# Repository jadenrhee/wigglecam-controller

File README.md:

# WiggleCam Camera Controller

The RP2040 board that handles timing-critical and analog work for a
[4-lens camera](https://github.com/jadenrhee/wigglecam). The Raspberry
Pi runs capture and image processing, but Linux is not a real-time OS
and the Pi can't drive the flash directly.

This board runs the LED flash at constant current, with the limits set
in the circuit rather than only in firmware. It also debounces the
shutter, decodes the EC11 encoder, and monitors battery voltage and
current through an INA219. On a trigger it pulses the Pi the instant the
LEDs reach full current.

The Pi drives it over I2C at 0x17, and the capture pulse returns on its
own GPIO line. The 2x6 header maps 1:1 onto Pi 5 GPIO pins 1 to 12.

Not fabricated yet, so everything here comes from the design files.

Signal routing, front copper red and back copper blue, planes hidden:

| | |
|---|---|
| Board | 76 x 50 mm, 4 layers |
| Schematic | ERC clean, 0 errors and 0 warnings |
| Layout | DRC clean, 0 violations and 0 unconnected, against JLCPCB's published 4-layer rules |
| Verification | 24 checks measured off the finished layout, no failures. [Report](docs/verification-report.md) |
| Firmware | builds clean under the Pico SDK |
| Fab outputs | Gerbers, drill, BOM, and placement files in [fab/](fab/); the ready-to-upload set is [fab/jlc/](fab/jlc/) |

## Repo layout

| Path | Contents |
|------|----------|
| [hardware/skidl/](hardware/skidl/) | schematic as code, the source of record |
| [hardware/kicad/](hardware/kicad/) | the board file and custom footprints |
| [hardware/partlist.md](hardware/partlist.md) | every part, the reasoning behind it, and where to order it |
| [fab/](fab/) | Gerbers, Excellon drill, `bom.csv`, `cpl.csv`, renders |
| [firmware/](firmware/) | C firmware: I2C register file, flash safety logic, INA219, EC11, WS2812 |
| [enclosure/](enclosure/) | 3D-printable pod holding the screen, this board, and the Pi 5 |
| [docs/](docs/) | [verification report](docs/verification-report.md), [design rationale](docs/design-rationale.md), and the [Pi protocol](docs/protocol.md) |

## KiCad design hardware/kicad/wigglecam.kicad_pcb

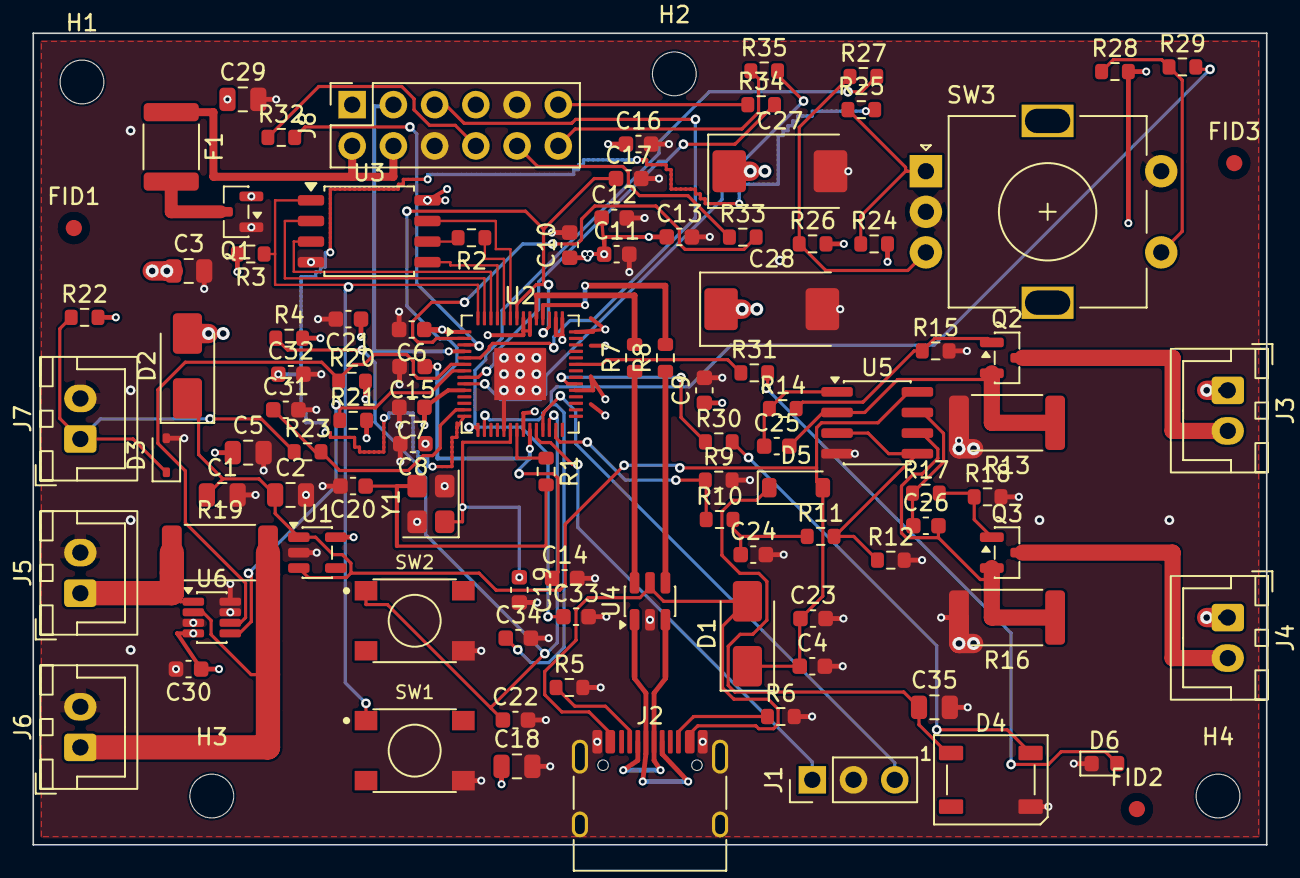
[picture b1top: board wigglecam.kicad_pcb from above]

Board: 4 copper layers, 76.0 x 50.0 mm, 105 parts (0 on the bottom side), 67 nets.

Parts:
C1, C2: 22uF; C_0805_2012Metric
C3, C5, C18, C29, C35: 10uF; C_0805_2012Metric
C4, C16, C17, C24: 1uF; C_0603_1608Metric
C6, C7, C8, C9, C10, C11, C12, C13, C14, C15, C21, C22, C23, C30, C31, C32, C33, C34: 100nF; C_0603_1608Metric
C19, C20: 15pF; C_0603_1608Metric
C25, C26: 1nF; C_0603_1608Metric
C27, C28: 470uF; CP_EIA-7343-30_AVX-N
D1, D2: SS34; D_SMA
D3: PESD5V0S1BA; D_SOD-323
D4: WS2812B; LED_WS2812B_PLCC4_5.0x5.0mm_P3.2mm
D5: 1N4148W; D_SOD-123
D6: GREEN; LED_0603_1608Metric
F1: PTC 3A; Fuse_1812_4532Metric
FID1, FID2, FID3: Fiducial_1mm_Mask2mm
H1, H2, H3, H4: MountingHole_2.7mm_M2.5
J1: SWD; PinHeader_1x03_P2.54mm_Vertical
J2: USB-C; USB_C_Receptacle_HRO_TYPE-C-31-M-12
J3: LED1; JST_XH_B2B-XH-A_1x02_P2.50mm_Vertical
J4: LED2; JST_XH_B2B-XH-A_1x02_P2.50mm_Vertical
J5: VBAT_IN; JST_XH_B2B-XH-A_1x02_P2.50mm_Vertical
J6: VBAT_OUT; JST_XH_B2B-XH-A_1x02_P2.50mm_Vertical
J7: SHUTTER; JST_XH_B2B-XH-A_1x02_P2.50mm_Vertical
J8: Pi GPIO 1-12; PinSocket_2x06_P2.54mm_Vertical
Q1: AO3401A; SOT-23
Q2, Q3: AO3400A; SOT-23
R1, R10, R23, R25, R27, R29, R31: 1k; R_0603_1608Metric
R2, R7, R8: 27R; R_0603_1608Metric
R3, R4, R22, R24, R26, R28: 10k; R_0603_1608Metric
R5, R6: 5.1k; R_0603_1608Metric
R9, R15, R18: 100k; R_0603_1608Metric
R11: 5.6k; R_0603_1608Metric
R12: 1.2k; R_0603_1608Metric
R13, R16: 0.5R 1%; R_2512_6332Metric
R14, R17: 100R; R_0603_1608Metric
R19: 10mR 2W 1%; R_2512_6332Metric
R20, R21: 4.7k; R_0603_1608Metric
R30: 470R; R_0603_1608Metric
R32, R33, R34, R35: 330R; R_0603_1608Metric
SW1, SW2: TACT; SW_TS-1187A_5.1x5.1mm
SW3: EC11; RotaryEncoder_Alps_EC11E-Switch_Vertical_H20mm
U1: AP2112K-3.3; SOT-23-5
U2: RP2040; QFN-56-1EP_7x7mm_P0.4mm_EP3.2x3.2mm
U3: W25Q128JVSIQ; SOIC-8_5.3x5.3mm_P1.27mm
U4: USBLC6-2SC6; SOT-23-6
U5: LM358; SOIC-8_3.9x4.9mm_P1.27mm
U6: INA219; SOT-23-8
Y1: 12MHz; Crystal_SMD_3225-4Pin_3.2x2.5mm

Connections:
+3V3: C5.1, C6.1, C7.1, C8.1, C9.1, C10.1, C11.1, C12.1, C13.1, C16.1, C18.1, C21.1, C30.1, R3.2, R4.2, R20.2, R21.2, R22.2, R24.2, R26.2, R28.2, U1.5, U2.1, U2.10, U2.22, U2.33, U2.42, U2.43, U2.44, U2.48, U2.49, U3.8, U6.4
CAM_SYNC: R34.2, U2.8
CAM_SYNC_HDR: J8.11, R34.1
ENC_A: C32.1, R25.2, U2.14
ENC_A_RAW: R24.1, R25.1, SW3.A
ENC_B: C33.1, R27.2, U2.15
ENC_B_RAW: R26.1, R27.1, SW3.B
ENC_SW1: C34.1, R29.2, U2.16
ENC_SW1_RAW: R28.1, R29.1, SW3.S1
FLASH_PWM: R9.1, R10.1, U2.27
GND: C1.2, C2.2, C3.2, C4.2, C5.2, C6.2, C7.2, C8.2, C9.2, C10.2, C11.2, C12.2, C13.2, C14.2, C15.2, C16.2, C17.2, C18.2, C19.2, C20.2, C21.2, C22.2, C23.2, C24.2, C27.2, C28.2, C29.2, C30.2, C31.2, C32.2, C33.2, C34.2, C35.2, D3.2, D4.3, D6.1, J1.2, J2.A1, J2.A12, J2.B1, J2.B12, J2.SH, J5.2, J6.2, J7.2, J8.6, J8.9, Q1.1, R5.2, R6.2, R9.2, R12.2, R13.2, R15.2, R16.2, R18.2, SW1.4, SW2.4, SW3.C, SW3.S2, U1.2, U2.19, U2.57, U3.4, U4.2, U5.4, U6.3, U6.7, U6.8, Y1.2, Y1.4
I2C0_SCL: R21.1, U2.7, U6.5
I2C0_SDA: R20.1, U2.6, U6.6
unnamed: J1.1, U2.24
unnamed: J1.3, U2.25
unnamed: J2.A5, R5.1
unnamed: J2.B5, R6.1
unnamed: C25.1, R14.1, U5.1
unnamed: Q2.1, R14.2, R15.1
unnamed: J3.2, Q2.3
unnamed: C26.1, R17.1, U5.7
unnamed: Q3.1, R17.2, R18.1
unnamed: J4.2, Q3.3
unnamed: R31.1, U2.37
unnamed: D6.2, R31.2
PI5V_FUSED: F1.2, Q1.3
PI5V_RAW: F1.1, J8.2, J8.4
PI_SCL: J8.5, U2.5
PI_SDA: J8.3, U2.4
QSPI_SCLK: R2.1, U2.52
QSPI_SCLK_FL: R2.2, U3.6
QSPI_SD0: U2.53, U3.5
QSPI_SD1: U2.55, U3.2
QSPI_SD2: U2.54, U3.3
QSPI_SD3: U2.51, U3.7
QSPI_SS: R3.1, SW1.1, U2.56, U3.1
RUN: C22.1, R4.1, SW2.1, U2.26
SENSE1: C25.2, Q2.2, R13.1, U5.2
SENSE2: C26.2, Q3.2, R16.1, U5.6
SHUTTER_N: C31.1, R23.2, U2.13
SHUTTER_RAW: D3.1, J7.1, R22.1, R23.1
SPARE_IO: R35.2, U2.9
SPARE_IO_HDR: J8.12, R35.1
UART_RX: R32.2, U2.3
UART_RX_HDR: J8.8, R32.1
UART_TX: R33.2, U2.2
UART_TX_HDR: J8.10, R33.1
USB_DM: R8.2, U2.46
USB_DM_CONN: J2.A7, J2.B7, U4.3
USB_DM_ESD: R8.1, U4.4
USB_DP: R7.2, U2.47
USB_DP_CONN: J2.A6, J2.B6, U4.1
USB_DP_ESD: R7.1, U4.6
VBAT_IN: J5.1, R19.1, U6.1
VBAT_OUT: J6.1, R19.2, U6.2
VBUS: D1.2, J2.A4, J2.A9, J2.B4, J2.B9, U4.5
VLED: C3.1, C27.1, C28.1, C29.1, D2.2, J3.1, J4.1, Q1.2
VREF: R11.2, R12.1, U5.3, U5.5
VREF_RAW: C24.1, R10.2, R11.1
VREG_1V1: C14.1, C15.1, C17.1, U2.23, U2.45, U2.50
VSYS: C1.1, C2.1, C4.1, C23.1, D1.1, D2.1, D5.2, U1.1, U1.3, U5.8
WS_DIN: R30.1, U2.34
WS_DIN_R: D4.4, R30.2
WS_VDD: C35.1, D4.1, D5.1
XIN: C19.1, U2.20, Y1.1
XOUT: R1.1, U2.21
XOUT_XTAL: C20.1, R1.2, Y1.3

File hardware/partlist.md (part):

# Part list (verified against LCSC stock, 2026-07-02)

Every named part below was individually confirmed present and in stock
at LCSC on the date above, except where a row says "confirm at order". Prices are the LCSC
from-price at qty 1; re-check stock at order time, it moves.
"JLC class" (basic vs extended, affects assembly setup fees) should be
confirmed in the JLCPCB BOM tool at order time; known classes noted.

**2026-07-03 update:** refdes corrected to match the routed board
(`fab/bom.csv` is the authoritative refdes source), generic-passive
picks added (each number verified against its LCSC product page for
value + package), and the 470 µF reservoir got its concrete pick.

## MCU core

| Ref | Part | Package | LCSC | ~$ | Notes |
|-----|------|---------|------|----|-------|
| U2 | [RP2040](https://www.lcsc.com/product-detail/C2040.html) | QFN-56 7×7 | **C2040** | 0.70 | in stock; support circuit per the official *Hardware design with RP2040* guide |
| U3 | [W25Q128JVSIQ](https://www.lcsc.com/product-detail/NOR-FLASH_Winbond-Elec-W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 16 MB QSPI | SOIC-8 | **C97521** | 0.47 | in stock; the flash used on the Pico |
| Y1 | [ABM8-272-T3](https://www.lcsc.com/product-detail/C20625731.html) 12 MHz, CL = 10 pF | 3225 | **C20625731** | 0.15 | in stock; the exact crystal from the RP2040 guide's minimal example → 15 pF load caps + 1 kΩ series R on XOUT, straight from the guide |
| SW1, SW2 | [TS-1187A-B-A-B](https://www.lcsc.com/product-detail/C318884.html) BOOTSEL + RUN | SMD 5.1 mm | **C318884** | 0.01 | in stock, JLC **basic**. Known deviation: no 1 kΩ in series with the BOOTSEL button (reference design has one) |
| J1 | SWD header 1×3, 2.54 mm | THT | generic | - | hand-solder; any vendor |

## Power

| Ref | Part | Package | LCSC | ~$ | Notes |
|-----|------|---------|------|----|-------|
| U1 | [AP2112K-3.3TRG1](https://www.lcsc.com/product-detail/C51118.html) 600 mA LDO | SOT-23-5 | **C51118** | 0.09 | in stock (131 k units) |
| Q1 | [AO3401A](https://www.lcsc.com/product-detail/C15127.html) P-ch, reverse-polarity protection | SOT-23 | **C15127** | 0.05 | in stock, JLC **basic**; polarity-critical in the JLC preview |
| D1, D2 | [SS34](https://www.lcsc.com/product-detail/C8678.html) 3 A Schottky, VBUS/VLED diode-OR | SMA | **C8678** | 0.03 | cathode bands polarity-critical in the JLC preview |
| F1 | [BSMD1812-300-16V](https://www.lcsc.com/product-detail/C883162.html) PTC, 3 A hold | 1812 | **C883162** | - | Pi-5V input fuse |

## USB-C

| Ref | Part | Package | LCSC | ~$ | Notes |
|-----|------|---------|------|----|-------|
| J2 | [TYPE-C-31-M-12](https://www.lcsc.com/product-detail/USB-Type-C_Korean-Hropar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 16-pin | SMD+THT shell | **C165948** | 0.10 | in stock; the de-facto hobby USB-C jack, hand-solderable |
| U4 | [USBLC6-2SC6](https://www.lcsc.com/product-detail/C7519.html) ESD array | SOT-23-6 | **C7519** | 0.08 | in stock; in D± path before the MCU |
| R7, R8 | 27 Ω 1 % D± series | 0603 | **C25190** | - | guide-nominal 27 Ω (Pico's 27.4 Ω is the E96 neighbour, equivalent at USB-FS); JLC **basic** |

## Flash driver (constant-current, discrete; see decision note below)

| Ref | Part | Package | LCSC | ~$ | Notes |
|-----|------|---------|------|----|-------|
| U5 | [LM358DR2G](https://www.lcsc.com/product-detail/General-Purpose-Amplifie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 dual op-amp | SOIC-8 | **C7950** | 0.03 | in stock, JLC **basic**; one half per LED branch |
| Q2, Q3 | [AO3400A](https://www.lcsc.com/product-detail/MOSFET_AOS_AO3400A_AO340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 N-ch sink FETs | SOT-23 | **C20917** | 0.05 | in stock, JLC **basic**; 150 ms pulse-thermal disposition in the verification report |
| R13, R16 | [RTT25R500FTE](https://www.lcsc.com/product-detail/C105149.html) 0.5 Ω 1 % 1 W sense | 2512 | **C105149** | 0.02 | 1 A per branch → 0.5 V sense; 0.5 W only during the ≤150 ms pulse |
| C27, C28 | [6TPE470MI](https://www.lcsc.com/product-detail/Tantalum-Capacitors_PANA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 470 µF 6.3 V 18 mΩ POSCAP | EIA-7343 | **C402828** | - | the low-ESR polymer reservoir the sizing math assumes; 6.3 V on a ~4.9 V rail ≈ 78 %, inside polymer derating practice |
| J3, J4 | [B2B-XH-A(LF)(SN)](https://www.lcsc.com/product-detail/C158012.html) JST-XH 2-pin, LED branches out | THT | **C158012** | - | genuine JST; LEDs (2× XP-G3 stars) live off-board at the flash window; hand-solder |

**Why a discrete sink instead of the AL8860:** the AL8860 is a *buck*
driver, so from a 5 V rail it cannot drive a 2-3-LED series string
(6-9 V); you'd need one AL8860 + inductor per LED, all JLC extended
parts. The discrete sink (LM358 + AO3400A + sense R, all JLC basic)
drives two parallel 1 A branches from 5 V at lower cost, with true
constant-current regulation. Reference for the sinks comes from an
RP2040 PWM pin through an RC filter (adjustable flash power); a
100 kΩ pulldown on that node holds the reference at 0 V during boot,
so the flash physically cannot fire until firmware drives it.

## Battery monitor

| Ref | Part | Package | LCSC | ~$ | Notes |
|-----|------|---------|------|----|-------|
| U6 | [INA219AIDCNR](https://www.lcsc.com/product-detail/C87469.html) | SOT-23-8 | **C87469** | 0.33 | in stock; on an internal I2C bus (RP2040 master), separate from the Pi-facing bus |
| R19 | [GX2512-2W-10mR-1%](https://jlcpcb.com/partdetail/Milliohm-GX2512_2W_10mR_1/C500718) shunt | 2512 2 W | **C500718** | - | in stock; 5 A → 50 mV drop, 0.25 W, inside the INA219 ±320 mV range |
| J5, J6 | [B2B-XH-A(LF)(SN)](https://www.lcsc.com/product-detail/C158012.html) JST-XH battery pass-through (in/out) | THT | **C158012** | - | battery lead routes through the shunt; can be left unpopulated and the leads soldered straight into the through-holes; hand-solder |

## Controls & status

| Ref | Part | Package | LCSC | ~$ | Notes |
|-----|------|---------|------|----|-------|
| J7, D3 | Shutter via [B2B-XH-A](https://www.lcsc.com/product-detail/C158012.html) JST-XH (panel button off-board) + RC debounce + [PESD5V0S1BA,115](https://www.lcsc.com/product-detail/C19224.html) TVS | THT / SOD-323 | **C158012** / **C19224** | - | TVS in stock (328 k units), Nexperia original |
| SW3 | [EC11E18244AU](https://www.lcsc.com/product-detail/C202365.html) rotary encoder w/ push | THT | **C202365** | - | in stock, genuine ALPS; shaft length vs enclosure = TODO(measure); hand-solder |
| D4 | [WS2812B-B/T](https://www.lcsc.com/product-detail/Light-Emitting-Diodes-LE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 status RGB | 5050 | **C2761795** | 0.05 | in stock at LCSC; reports exist of JLC assembly rejecting the 5050 variant; hand-solder fallback (easy). VDD fed through a 1N4148 drop (~4.3 V) so 3.3 V data meets the 0.7·VDD input threshold |
| D5 | [1N4148W](https://www.lcsc.com/product-detail/C81598.html) WS2812 VDD drop | SOD-123 | **C81598** | - | |
| D6 | [Green LED](https://www.lcsc.com/product-detail/C72043.html) debug, GPIO25 | 0603 | **C72043** | - | |
| J8 | 2×6 female socket, 2.54 mm, Pi interface | THT | generic | - | maps 1:1 onto Pi 5 GPIO pins 1-12, see below; hand-solder; any vendor |

## Generic passives (JLC picks, value + package verified 2026-07-03)

All 0603/0805 lines are JLC-basic-class commodity parts; refdes
groupings match `fab/bom.csv`.

| Value | Refs | Package | LCSC | Part |
|-------|------|---------|------|------|
| 100 nF X7R 50 V | C6-C15, C21-C23, C30-C34 (×18) | 0603 | **C14663** | YAGEO CC0603KRX7R9BB104 |
| 1 µF X5R | C4, C16, C17, C24 | 0603 | **C15849** | Samsung CL10A105KB8NNNC |
| 15 pF C0G 50 V (crystal load) | C19, C20 | 0603 | **C1644** | Samsung CL10C150JB8NNNC |
| 1 nF X7R (comp) | C25, C26 | 0603 | **C1588** | Samsung CL10B102KB8NNNC |
| 10 µF X5R 25 V | C3, C5, C18, C29, C35 | 0805 | **C15850** | Samsung CL21A106KAYNNNE |
| 22 µF X5R 25 V (VSYS bulk) | C1, C2 | 0805 | **C45783** | Samsung CL21A226MAQNNNE |
| 27 Ω 1 % | R2, R7, R8 | 0603 | **C25190** | UNI-ROYAL |
| 100 Ω 1 % | R14, R17 | 0603 | **C22775** | UNI-ROYAL 0603WAF1000T5E |
| 330 Ω 1 % | R32-R35 | 0603 | **C23138** | UNI-ROYAL 0603WAF3300T5E |
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
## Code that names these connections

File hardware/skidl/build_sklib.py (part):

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            Pin(num='17',name='GPIO14',func=pin_types.BIDIR),
            Pin(num='18',name='GPIO15',func=pin_types.BIDIR),
            Pin(num='19',name='TESTEN',func=pin_types.INPUT),
            Pin(num='20',name='XIN',func=pin_types.INPUT),
            Pin(num='21',name='XOUT',func=pin_types.OUTPUT),
            Pin(num='22',name='IOVDD',func=pin_types.PWRIN),
            Pin(num='23',name='DVDD',func=pin_types.PWRIN),
            Pin(num='24',name='SWCLK',func=pin_types.INPUT),
            Pin(num='25',name='SWDIO',func=pin_types.BIDIR),
            Pin(num='26',name='RUN',func=pin_types.INPUT),
            Pin(num='27',name='GPIO16',func=pin_types.BIDIR),
            Pin(num='28',name='GPIO17',func=pin_types.BIDIR),
            Pin(num='29',name='GPIO18',func=pin_types.BIDIR),
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            Pin(num='43',name='ADC_AVDD',func=pin_types.PWRIN),
            Pin(num='44',name='VREG_VIN',func=pin_types.PWRIN),
            Pin(num='45',name='VREG_VOUT',func=pin_types.PWROUT),
            Pin(num='46',name='USB_DM',func=pin_types.BIDIR),
            Pin(num='47',name='USB_DP',func=pin_types.BIDIR),
            Pin(num='48',name='USB_VDD',func=pin_types.PWRIN),
            Pin(num='49',name='IOVDD',func=pin_types.PWRIN),
            Pin(num='50',name='DVDD',func=pin_types.PWRIN),
            Pin(num='51',name='QSPI_SD3',func=pin_types.BIDIR),
            Pin(num='52',name='QSPI_SCLK',func=pin_types.OUTPUT),
            Pin(num='53',name='QSPI_SD0',func=pin_types.BIDIR),
            Pin(num='54',name='QSPI_SD2',func=pin_types.BIDIR),
            Pin(num='55',name='QSPI_SD1',func=pin_types.BIDIR),
            Pin(num='56',name='QSPI_SS_N',func=pin_types.OUTPUT),
            Pin(num='57',name='GND',func=pin_types.PWRIN)] }),
        Part(**{ 'name':'W25Q128JVSIQ', 'dest':TEMPLATE, 'tool':SKIDL, 'aliases':Alias({'W25Q128JVSIQ'}), 'ref_prefix':'U', 'fplist':None, 'footprint':'Package_SO:SOIC-8_5.23x5.23mm_P1.27mm', 'keywords':None, 'description':'', 'datasheet':None, 'pins':[
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        Part(**{ 'name':'R_shunt', 'dest':TEMPLATE, 'tool':SKIDL, 'aliases':Alias({'R_shunt'}), 'ref_prefix':'R', 'fplist':None, 'footprint':'Resistor_SMD:R_2512_6332Metric', 'keywords':None, 'description':'', 'datasheet':None, 'pins':[
            Pin(num='1',name='1',func=pin_types.PASSIVE),
            Pin(num='2',name='2',func=pin_types.PASSIVE)] }),
        Part(**{ 'name':'VBAT_IN', 'dest':TEMPLATE, 'tool':SKIDL, 'aliases':Alias({'VBAT_IN'}), 'ref_prefix':'J', 'fplist':None, 'footprint':'Connector_JST:JST_XH_B2B-XH-A_1x02_P2.50mm_Vertical', 'keywords':None, 'description':'', 'datasheet':None, 'pins':[
            Pin(num='1',name='1',func=pin_types.PASSIVE),
            Pin(num='2',name='2',func=pin_types.PASSIVE)] }),
        Part(**{ 'name':'VBAT_OUT', 'dest':TEMPLATE, 'tool':SKIDL, 'aliases':Alias({'VBAT_OUT'}), 'ref_prefix':'J', 'fplist':None, 'footprint':'Connector_JST:JST_XH_B2B-XH-A_1x02_P2.50mm_Vertical', 'keywords':None, 'description':'', 'datasheet':None, 'pins':[
            Pin(num='1',name='1',func=pin_types.PASSIVE),
            Pin(num='2',name='2',func=pin_types.PASSIVE)] }),
        Part(**{ 'name':'SHUTTER', 'dest':TEMPLATE, 'tool':SKIDL, 'aliases':Alias({'SHUTTER'}), 'ref_prefix':'J', 'fplist':None, 'footprint':'Connector_JST:JST_XH_B2B-XH-A_1x02_P2.50mm_Vertical', 'keywords':None, 'description':'', 'datasheet':None, 'pins':[
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
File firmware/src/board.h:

// Pin map. Must match hardware/skidl/circuit.py exactly.
#pragma once

#define PIN_UART_TX      0   // -> Pi RXD (GPIO15)
#define PIN_UART_RX      1   // <- Pi TXD (GPIO14)
#define PIN_I2C_SLAVE_SDA 2  // Pi I2C1 (Pi GPIO2)
#define PIN_I2C_SLAVE_SCL 3  // Pi I2C1 (Pi GPIO3)
#define PIN_I2C_INT_SDA  4   // internal bus: INA219
#define PIN_I2C_INT_SCL  5
#define PIN_CAM_SYNC     6   // -> Pi GPIO17, capture-sync pulse
#define PIN_ATTN         7   // -> Pi GPIO18, "event pending" flag
#define PIN_SHUTTER      10  // active low, RC-conditioned
#define PIN_ENC_A        11
#define PIN_ENC_B        12
#define PIN_ENC_SW       13  // active low
#define PIN_FLASH_PWM    16  // filtered PWM -> current-sink reference
#define PIN_WS2812       22
#define PIN_DEBUG_LED    25

#define I2C_SLAVE_ADDR   0x17
#define INA219_ADDR      0x40

// Flash safety limits (mirror the hardware: 100k pulldown keeps the
// reference at 0 V until firmware drives it)
#define FLASH_MAX_MS     150
#define FLASH_COOLDOWN_MS 800

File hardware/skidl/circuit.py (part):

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# ---------------------------------------------------------------- nets ----
GND = Net("GND"); GND.drive = POWER
VBUS = Net("VBUS")            # USB-C 5 V (bench power)
PI5V_RAW = Net("PI5V_RAW")    # 5 V from Pi header, pre-protection
VSYS = Net("VSYS")            # diode-OR of VBUS/VLED → logic supply
VSYS.drive = POWER            # driven through the OR diodes (skidl
                              # doesn't propagate drive through parts)
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VBAT_IN = Net("VBAT_IN")      # battery pass-through, shunt high side
VBAT_OUT = Net("VBAT_OUT")    # battery pass-through, shunt low side

for n in (VBUS, PI5V_RAW):
    n.drive = POWER


def power_input():
    """USB-C + Pi 5 V inputs → VSYS; reverse-polarity protected.

    Pi path: PI5V_RAW → F1 (PTC 3 A hold) → Q1 AO3401A (drain=input,
    source=load, gate=GND: body diode conducts at first power, channel
    then enhances with Vgs=-5 V; on reversed input both diode and
    channel block) → VLED → D2 → VSYS.
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    q1 = P.AO3401A()
    d1, d2 = P.SS34(), P.SS34()

    fused = Net("PI5V_FUSED")
    f1[1] += PI5V_RAW; f1[2] += fused
    q1["D"] += fused
    q1["S"] += VLED
    q1["G"] += GND     # gate hard to GND: textbook P-FET reverse guard
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    GPIO2/3, board adds none)."""
    j = P.PI_HDR()
    j["P1"] += NC                # Pi 3V3, reference only, unused
    j["P2"] += PI5V_RAW
    j["P4"] += PI5V_RAW
    j["P6"] += GND
    j["P9"] += GND
    j["P7"] += NC                # Pi GPIO4, spare, unused
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        n1, n2 = Net(name + "_HDR"), Net(name)
        a += n1; r[1] += n1; r[2] += n2; b += n2

    series("UART_RX", j["P8"], u["GPIO1"])    # Pi TXD → RP2040 RX
    series("UART_TX", j["P10"], u["GPIO0"])   # RP2040 TX → Pi RXD
    series("CAM_SYNC", j["P11"], u["GPIO6"])  # sync pulse → Pi GPIO17
    series("SPARE_IO", j["P12"], u["GPIO7"])  # ↔ Pi GPIO18; carries ATTN (see docs/protocol.md), net name predates the routed board

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
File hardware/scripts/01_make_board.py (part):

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    (56.9, 24.9, 59.4, 26.3),   # sense-R GND via pocket, branch A
    (56.9, 36.9, 59.4, 38.3),   # sense-R GND via pocket, branch B
    (13.4, 31.0, 15.4, 46.4),   # VBAT_OUT heavy trace column
    (2.0, 41.6, 15.4, 46.4),    # VBAT_OUT row to J6 (either pin row)
    (2.0, 32.8, 9.6, 34.7),     # VBAT_IN heavy trace row
]

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        if (pads[net][axis] > pads[other][axis]) == want_less:
            fp.SetOrientationDegrees(fp.GetOrientationDegrees() + 180)

    fixup(fps["F1"], "PI5V_RAW", "north")
    fixup(fps["D2"], "VLED", "north")
    fixup(fps["J3"], "VLED", "north")
    fixup(fps["J4"], "VLED", "north")
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        orient_cap_toward(ref, "+3V3", px, py)
        placed.add(ref)

    # DVDD (VREG_1V1) caps → pins 23 and 50; 1 µF pair → pins 44/45
    special = [
        (lambda p: p["value"] == "100nF" and
            netsig(p) == frozenset({"VREG_1V1", "GND"}),
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    for p in bridge["parts"]:
        for padnum, net in p["pads"].items():
            netpads.setdefault(net, []).append((p["ref"], padnum))
    POWERISH = {"GND", "+3V3", "VSYS", "VLED", "VBUS", "PI5V_RAW"}

    remaining = [p for p in bridge["parts"] if p["ref"] not in placed]
    # place parts on fewer-pad (more specific) nets first
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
